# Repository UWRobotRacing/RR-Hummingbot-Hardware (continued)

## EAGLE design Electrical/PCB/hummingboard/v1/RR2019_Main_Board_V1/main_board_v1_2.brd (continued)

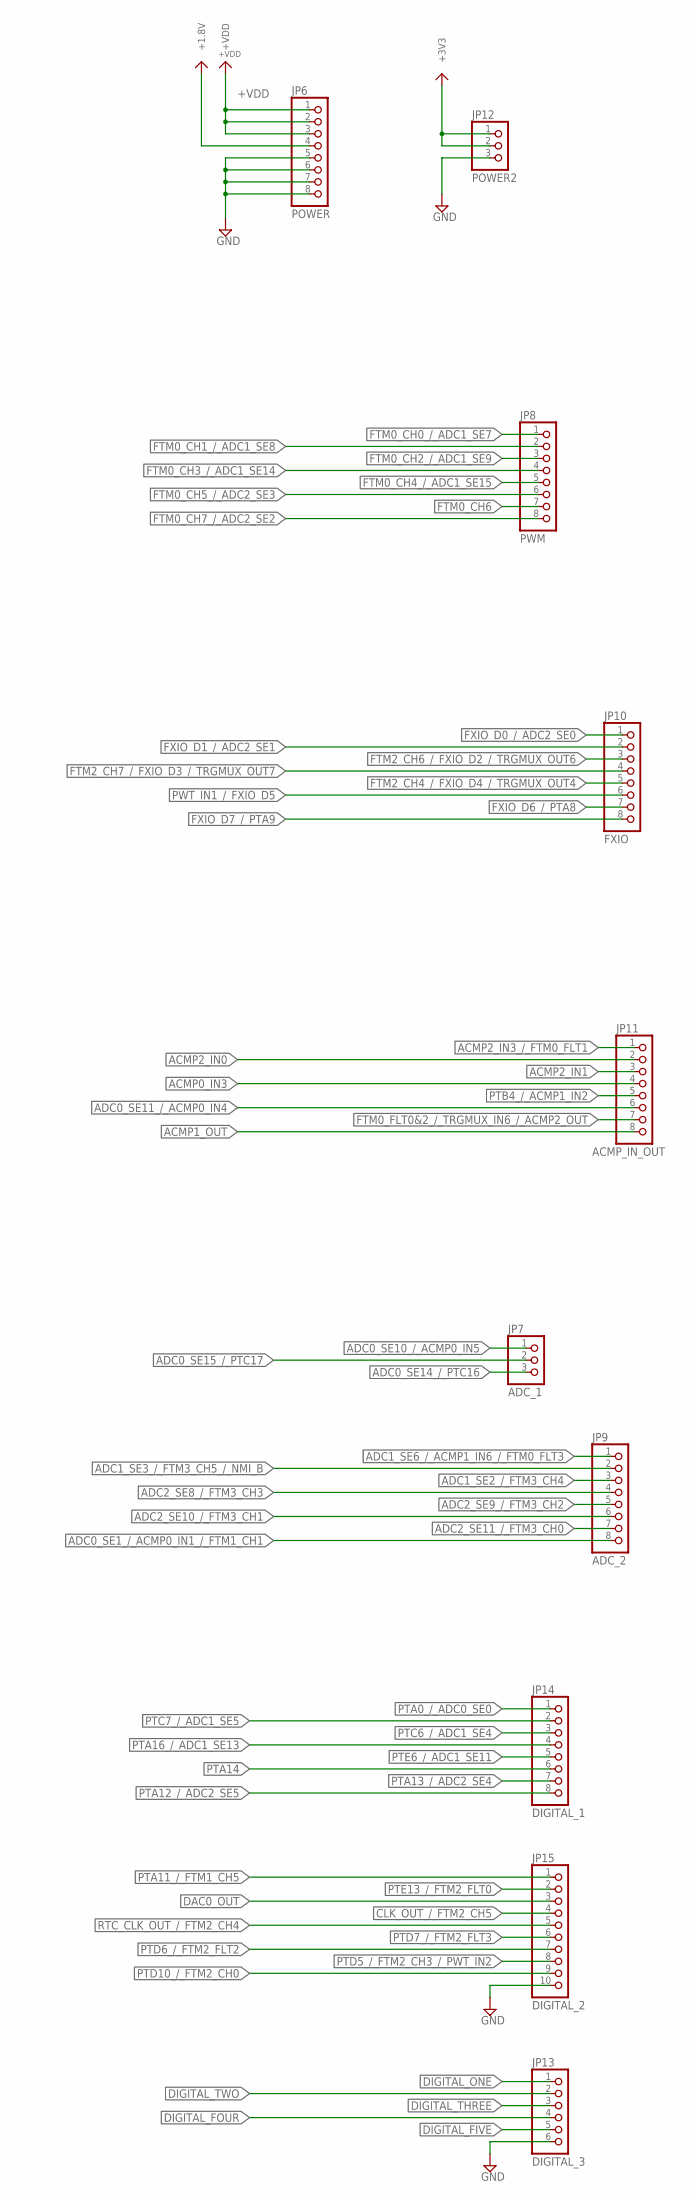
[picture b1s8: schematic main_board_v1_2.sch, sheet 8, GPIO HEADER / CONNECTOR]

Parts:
JP6: POWER; 1X08-BIG
JP7: ADC_1; 1X03
JP8: PWM; 1X08-BIG
JP9: ADC_2; 1X08-BIG
JP10: FXIO; 1X08-BIG
JP11: ACMP_IN_OUT; 1X08-BIG
JP12: POWER2; 1X03
JP13: DIGITAL_3; 1X06-BIG
JP14: DIGITAL_1; 1X08-BIG
JP15: DIGITAL_2; 1X10-BIG

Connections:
+1.8V: JP6.4; also elsewhere on the board
+3V3: JP12.1, JP12.2; also elsewhere on the board
+VDD: JP6.1, JP6.2, JP6.3; also elsewhere on the board
ACMP0_IN3: JP11.4; also elsewhere on the board
ACMP1_OUT: JP11.8; also elsewhere on the board
ACMP2_IN0: JP11.2; also elsewhere on the board
ACMP2_IN1: JP11.3; also elsewhere on the board
ACMP2_IN3_/_FTM0_FLT1: JP11.1; also elsewhere on the board
ADC0_SE1_/_ACMP0_IN1_/_FTM1_CH1: JP9.8; also elsewhere on the board
ADC0_SE10_/_ACMP0_IN5: JP7.1; also elsewhere on the board
ADC0_SE11_/_ACMP0_IN4: JP11.6; also elsewhere on the board
ADC0_SE14_/_PTC16: JP7.3; also elsewhere on the board
ADC0_SE15_/_PTC17: JP7.2; also elsewhere on the board
ADC1_SE2_/_FTM3_CH4: JP9.3; also elsewhere on the board
ADC1_SE3_/_FTM3_CH5_/_NMI_B: JP9.2; also elsewhere on the board
ADC1_SE6_/_ACMP1_IN6_/_FTM0_FLT3: JP9.1; also elsewhere on the board
ADC2_SE8_/_FTM3_CH3: JP9.4; also elsewhere on the board
ADC2_SE9_/_FTM3_CH2: JP9.5; also elsewhere on the board
ADC2_SE10_/_FTM3_CH1: JP9.6; also elsewhere on the board
ADC2_SE11_/_FTM3_CH0: JP9.7; also elsewhere on the board
CLK_OUT_/_FTM2_CH5: JP15.4; also elsewhere on the board
DAC0_OUT: JP15.3; also elsewhere on the board
DIGITAL_FIVE: JP13.5; also elsewhere on the board
DIGITAL_FOUR: JP13.4; also elsewhere on the board
DIGITAL_ONE: JP13.1; also elsewhere on the board
DIGITAL_THREE: JP13.3; also elsewhere on the board
DIGITAL_TWO: JP13.2; also elsewhere on the board
FTM0_CH0_/_ADC1_SE7: JP8.1; also elsewhere on the board
FTM0_CH1_/_ADC1_SE8: JP8.2; also elsewhere on the board
FTM0_CH2_/_ADC1_SE9: JP8.3; also elsewhere on the board
FTM0_CH3_/_ADC1_SE14: JP8.4; also elsewhere on the board
FTM0_CH4_/_ADC1_SE15: JP8.5; also elsewhere on the board
FTM0_CH5_/_ADC2_SE3: JP8.6; also elsewhere on the board
FTM0_CH6: JP8.7; also elsewhere on the board
FTM0_CH7_/_ADC2_SE2: JP8.8; also elsewhere on the board
FTM0_FLT0&2_/_TRGMUX_IN6_/_ACMP2_OUT: JP11.7; also elsewhere on the board
FTM2_CH4_/_FXIO_D4_/_TRGMUX_OUT4: JP10.5; also elsewhere on the board
FTM2_CH6_/_FXIO_D2_/_TRGMUX_OUT6: JP10.3; also elsewhere on the board
FTM2_CH7_/_FXIO_D3_/_TRGMUX_OUT7: JP10.4; also elsewhere on the board
FXIO_D0_/_ADC2_SE0: JP10.1; also elsewhere on the board
FXIO_D1_/_ADC2_SE1: JP10.2; also elsewhere on the board
FXIO_D6_/_PTA8: JP10.7; also elsewhere on the board
FXIO_D7_/_PTA9: JP10.8; also elsewhere on the board
GND: JP6.5, JP6.6, JP6.7, JP6.8, JP12.3, JP13.6, JP15.10; also elsewhere on the board
PTA0_/_ADC0_SE0: JP14.1; also elsewhere on the board
PTA11_/_FTM1_CH5: JP15.1; also elsewhere on the board
PTA12_/_ADC2_SE5: JP14.8; also elsewhere on the board
PTA13_/_ADC2_SE4: JP14.7; also elsewhere on the board
PTA14: JP14.6; also elsewhere on the board
PTA16_/_ADC1_SE13: JP14.4; also elsewhere on the board
PTB4_/_ACMP1_IN2: JP11.5; also elsewhere on the board
PTC6_/_ADC1_SE4: JP14.3; also elsewhere on the board
PTC7_/_ADC1_SE5: JP14.2; also elsewhere on the board
PTD5_/_FTM2_CH3_/_PWT_IN2: JP15.8; also elsewhere on the board
PTD6_/_FTM2_FLT2: JP15.7; also elsewhere on the board
PTD7_/_FTM2_FLT3: JP15.6; also elsewhere on the board
PTD10_/_FTM2_CH0: JP15.9; also elsewhere on the board
PTE6_/_ADC1_SE11: JP14.5; also elsewhere on the board
PTE13_/_FTM2_FLT0: JP15.2; also elsewhere on the board
PWT_IN1_/_FXIO_D5: JP10.6; also elsewhere on the board
RTC_CLK_OUT_/_FTM2_CH4: JP15.5; also elsewhere on the board

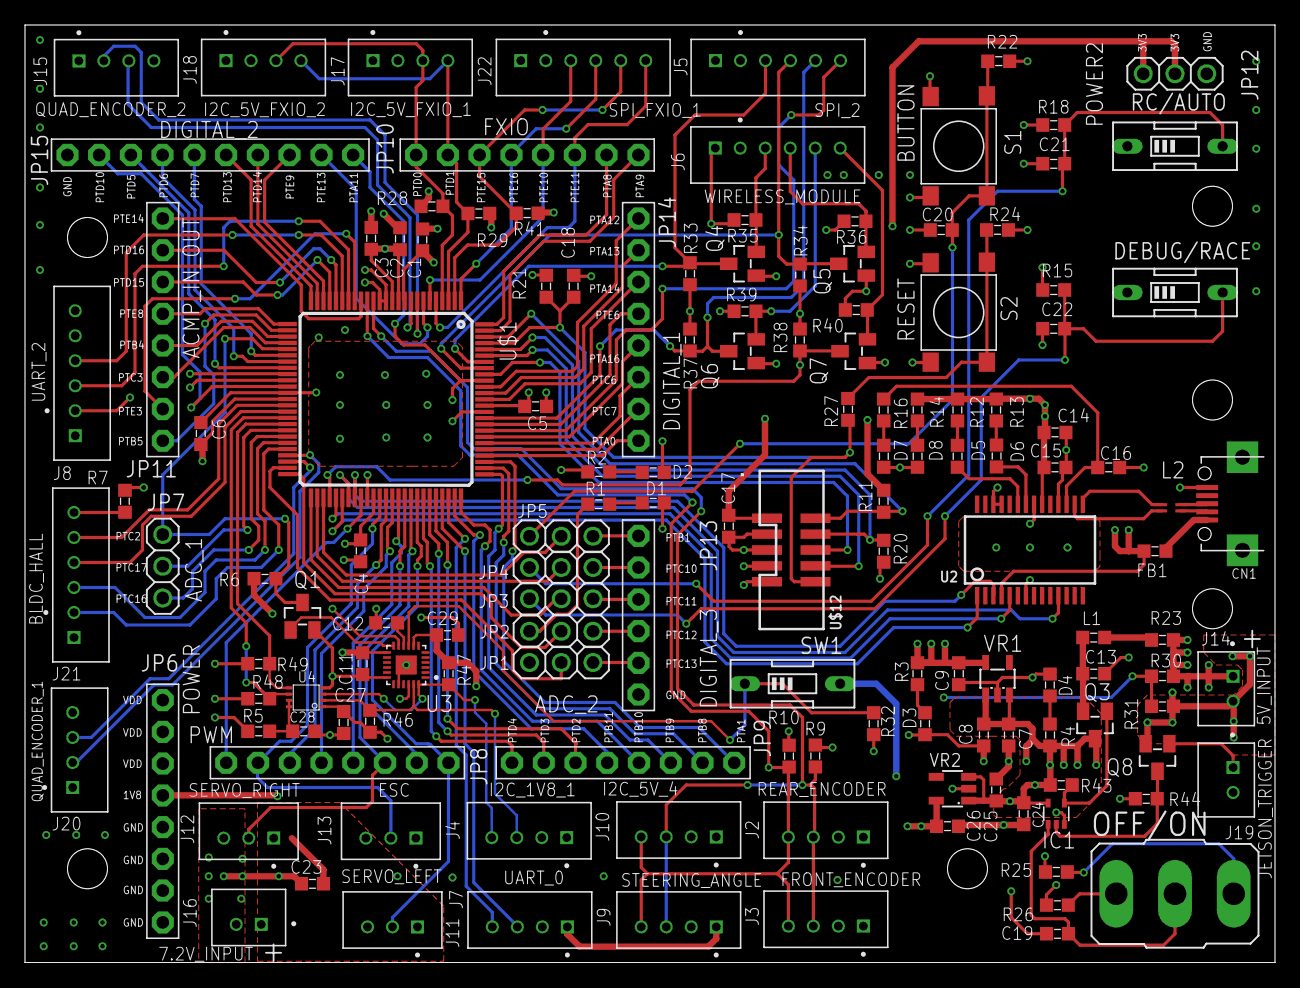
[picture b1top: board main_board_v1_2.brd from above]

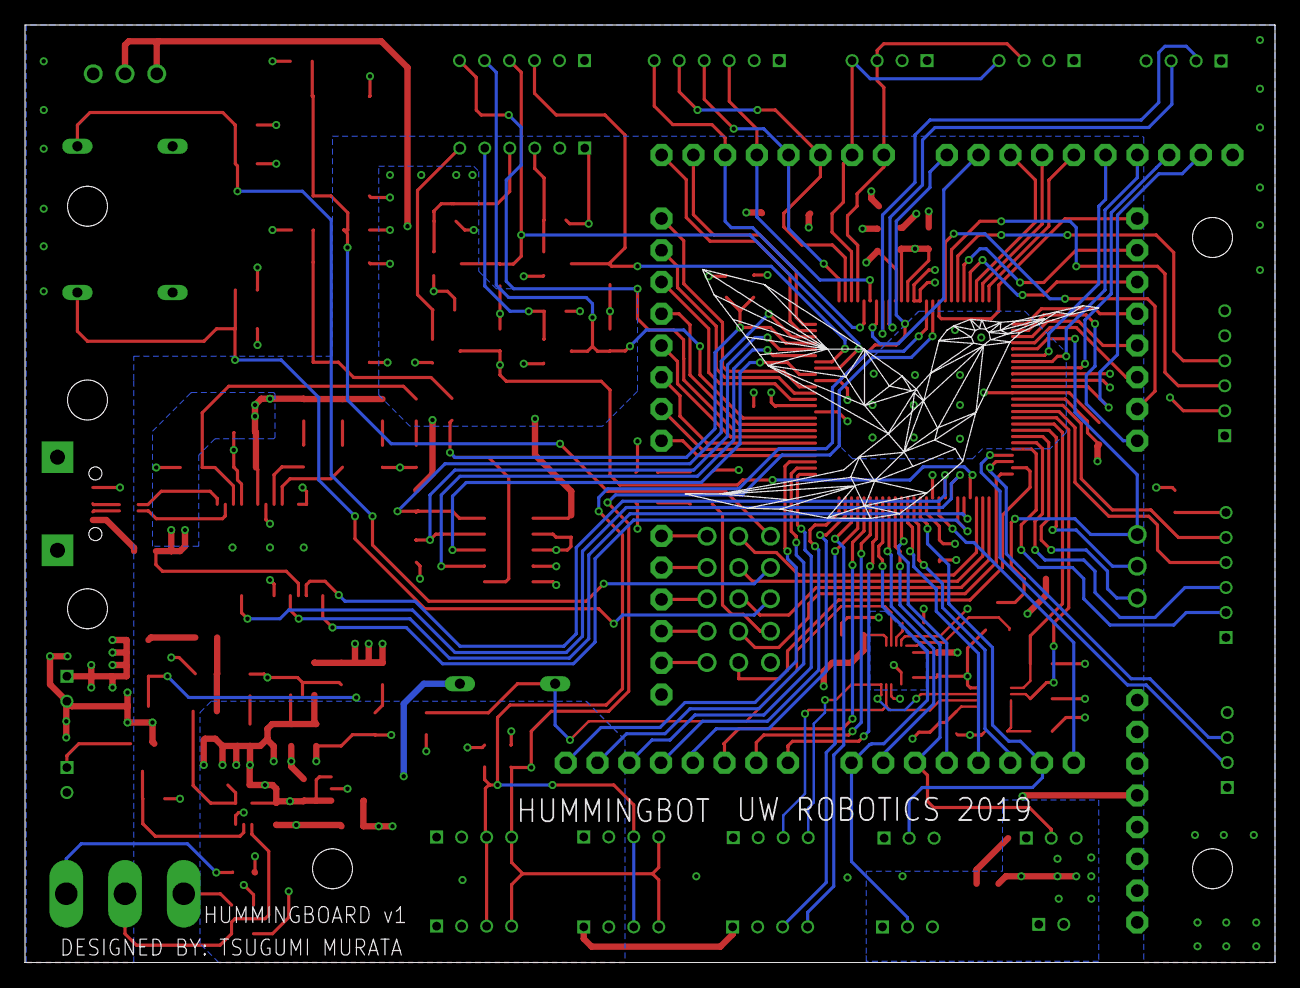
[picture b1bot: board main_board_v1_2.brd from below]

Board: 4 copper layers, 100.0 x 75.0 mm, 143 parts (2 on the bottom side), 142 nets.

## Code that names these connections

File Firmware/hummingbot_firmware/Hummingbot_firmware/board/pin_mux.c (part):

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BOARD_InitPins:
- options: {callFromInitBoot: 'true', coreID: core0, enableClock: 'true'}
- pin_list:
  - {pin_num: '1', peripheral: FLEXIO, signal: 'D, 3', pin_signal: PTE16/FTM2_CH7/FXIO_D3/TRGMUX_OUT7}
  - {pin_num: '2', peripheral: FLEXIO, signal: 'D, 2', pin_signal: PTE15/FTM2_CH6/FXIO_D2/TRGMUX_OUT6}
  - {pin_num: '3', peripheral: FLEXIO, signal: 'D, 1', pin_signal: ADC2_SE1/PTD1/FTM0_CH3/LPSPI1_SIN/FTM2_CH1/FXIO_D1/TRGMUX_OUT2}
  - {pin_num: '4', peripheral: FLEXIO, signal: 'D, 0', pin_signal: ADC2_SE0/PTD0/FTM0_CH2/LPSPI1_SCK/FTM2_CH0/FXIO_D0/TRGMUX_OUT1}
  - {pin_num: '5', peripheral: FLEXIO, signal: 'D, 5', pin_signal: ADC2_SE13/PTE11/PWT_IN1/LPTMR0_ALT1/FTM2_CH5/FXIO_D5/TRGMUX_OUT5}
  - {pin_num: '6', peripheral: FLEXIO, signal: 'D, 4', pin_signal: ADC2_SE12/PTE10/CLKOUT/FTM2_CH4/FXIO_D4/TRGMUX_OUT4}
  - {pin_num: '7', peripheral: GPIOE, signal: 'GPIO, 13', pin_signal: PTE13/FTM2_FLT0}
  - {pin_num: '8', peripheral: FTM2, signal: 'QD_PH, A', pin_signal: PTE5/TCLK2/FTM2_QD_PHA/FTM2_CH3/FXIO_D7/EWM_IN}
  - {pin_num: '9', peripheral: FTM2, signal: 'QD_PH, B', pin_signal: PTE4/BUSOUT/FTM2_QD_PHB/FTM2_CH2/FXIO_D6/EWM_OUT_b}
  - {pin_num: '10', peripheral: SUPPLY, signal: 'VDD, 0', pin_signal: VDD10}
  - {pin_num: '14', peripheral: SUPPLY, signal: 'VSS, 1', pin_signal: VSS15}
  - {pin_num: '15', peripheral: LPI2C0, signal: SCL, pin_signal: EXTAL/PTB7/LPI2C0_SCL}
  - {pin_num: '16', peripheral: LPI2C0, signal: SDA, pin_signal: XTAL/PTB6/LPI2C0_SDA}
  - {pin_num: '17', peripheral: CMP2, signal: 'IN, 3', pin_signal: ACMP2_IN3/PTE14/FTM0_FLT1/FTM2_FLT1}
  - {pin_num: '18', peripheral: CMP2, signal: OUT, pin_signal: PTE3/FTM0_FLT0/LPUART2_RTS/FTM2_FLT0/TRGMUX_IN6/ACMP2_OUT}
  - {pin_num: '19', peripheral: LPUART2, signal: TX, pin_signal: PTE12/FTM0_FLT3/LPUART2_TX}
  - {pin_num: '20', peripheral: LPUART2, signal: RX, pin_signal: PTD17/FTM0_FLT2/LPUART2_RX}
  - {pin_num: '21', peripheral: CMP2, signal: 'IN, 0', pin_signal: ACMP2_IN0/PTD16/FTM0_CH1}
  - {pin_num: '22', peripheral: CMP2, signal: 'IN, 1', pin_signal: ACMP2_IN1/PTD15/FTM0_CH0}
  - {pin_num: '23', peripheral: DAC0, signal: OUT, pin_signal: ACMP2_IN2/DAC0_OUT/PTE9/FTM0_CH7/LPUART2_CTS}
  - {pin_num: '24', peripheral: FTM2, signal: 'CH, 5', pin_signal: PTD14/FTM2_CH5/CLKOUT}
  - {pin_num: '25', peripheral: FTM2, signal: 'CH, 4', pin_signal: PTD13/FTM2_CH4/RTC_CLKOUT}
  - {pin_num: '26', peripheral: CMP0, signal: 'IN, 3', pin_signal: ACMP0_IN3/PTE8/FTM0_CH6}
  - {pin_num: '27', peripheral: CMP1, signal: OUT, pin_signal: PTB5/FTM0_CH5/LPSPI0_PCS1/TRGMUX_IN0/ACMP1_OUT}
  - {pin_num: '28', peripheral: CMP1, signal: 'IN, 2', pin_signal: ACMP1_IN2/PTB4/FTM0_CH4/LPSPI0_SOUT/TRGMUX_IN1}
  - {pin_num: '29', peripheral: CMP0, signal: 'IN, 4', pin_signal: ADC0_SE11/ACMP0_IN4/EXTAL32/PTC3/FTM0_CH3}
  - {pin_num: '30', peripheral: ADC0, signal: 'SE, 10', pin_signal: ADC0_SE10/ACMP0_IN5/XTAL32/PTC2/FTM0_CH2}
  - {pin_num: '31', peripheral: GPIOD, signal: 'GPIO, 7', pin_signal: PTD7/LPUART2_TX/FTM2_FLT3}
  - {pin_num: '32', peripheral: GPIOD, signal: 'GPIO, 6', pin_signal: PTD6/LPUART2_RX/FTM2_FLT2}
  - {pin_num: '33', peripheral: GPIOD, signal: 'GPIO, 5', pin_signal: PTD5/FTM2_CH3/LPTMR0_ALT2/FTM2_FLT1/PWT_IN2/TRGMUX_IN7}
  - {pin_num: '34', peripheral: LPUART2, signal: RTS, pin_signal: PTD12/FTM2_CH2/LPI2C1_HREQ/LPUART2_RTS}
  - {pin_num: '35', peripheral: LPUART2, signal: CTS, pin_signal: PTD11/FTM2_CH1/FTM2_QD_PHA/LPUART2_CTS}
  - {pin_num: '36', peripheral: GPIOD, signal: 'GPIO, 10', pin_signal: PTD10/FTM2_CH0/FTM2_QD_PHB}
  - {pin_num: '37', peripheral: SUPPLY, signal: 'VSS, 2', pin_signal: VSS38}
  - {pin_num: '39', peripheral: FTM1, signal: 'CH, 7', pin_signal: ADC0_SE9/ACMP1_IN3/PTC1/FTM0_CH1/FTM1_CH7}
  - {pin_num: '38', peripheral: SUPPLY, signal: 'VDD, 1', pin_signal: VDD39}
  - {pin_num: '40', peripheral: FTM1, signal: 'CH, 6', pin_signal: ADC0_SE8/ACMP1_IN4/PTC0/FTM0_CH0/FTM1_CH6}
  - {pin_num: '41', peripheral: LPI2C1, signal: SCL, pin_signal: ACMP1_IN5/PTD9/LPI2C1_SCL/FTM2_FLT3/FTM1_CH5}
  - {pin_num: '42', peripheral: LPI2C1, signal: SDA, pin_signal: PTD8/LPI2C1_SDA/FTM2_FLT2/FTM1_CH4}
  - {pin_num: '43', peripheral: ADC0, signal: 'SE, 15', pin_signal: ADC0_SE15/PTC17/FTM1_FLT3/LPI2C1_SCLS}
  - {pin_num: '44', peripheral: ADC0, signal: 'SE, 14', pin_signal: ADC0_SE14/PTC16/FTM1_FLT2/LPI2C1_SDAS}
  - {pin_num: '45', peripheral: FTM1, signal: 'CH, 3', pin_signal: ADC0_SE13/ACMP2_IN4/PTC15/FTM1_CH3}
  - {pin_num: '46', peripheral: FTM1, signal: 'CH, 2', pin_signal: ADC0_SE12/ACMP2_IN5/PTC14/FTM1_CH2}
  - {pin_num: '47', peripheral: FTM1, signal: 'QD_PH, A', pin_signal: ADC0_SE7/PTB3/FTM1_CH1/LPSPI0_SIN/FTM1_QD_PHA/TRGMUX_IN2}
  - {pin_num: '48', peripheral: FTM1, signal: 'QD_PH, B', pin_signal: ADC0_SE6/PTB2/FTM1_CH0/LPSPI0_SCK/FTM1_QD_PHB/TRGMUX_IN3}
  - {pin_num: '49', peripheral: GPIOC, signal: 'GPIO, 13', pin_signal: PTC13/FTM3_CH7/FTM2_CH7}
  - {pin_num: '50', peripheral: GPIOC, signal: 'GPIO, 12', pin_signal: PTC12/FTM3_CH6/FTM2_CH6}
  - {pin_num: '51', peripheral: GPIOC, signal: 'GPIO, 11', pin_signal: PTC11/FTM3_CH5}
  - {pin_num: '52', peripheral: GPIOC, signal: 'GPIO, 10', pin_signal: PTC10/FTM3_CH4}
  - {pin_num: '53', peripheral: GPIOB, signal: 'GPIO, 1', pin_signal: ADC0_SE5/ADC1_SE15/PTB1/LPUART0_TX/LPSPI0_SOUT/TCLK0}
  - {pin_num: '54', peripheral: LPSPI0, signal: PCS0, pin_signal: ADC0_SE4/ADC1_SE14/PTB0/LPUART0_RX/LPSPI0_PCS0/LPTMR0_ALT3/PWT_IN3}
  - {pin_num: '55', peripheral: LPUART1, signal: TX, pin_signal: ADC2_SE15/PTC9/LPUART1_TX/FTM1_FLT1/LPUART0_RTS}
  - {pin_num: '56', peripheral: LPUART1, signal: RX, pin_signal: ADC2_SE14/PTC8/LPUART1_RX/FTM1_FLT0/LPUART0_CTS}
  - {pin_num: '57', peripheral: LPUART1, signal: RTS, pin_signal: ADC0_SE3/ACMP1_IN1/PTA7/FTM0_FLT2/RTC_CLKIN/LPUART1_RTS}
  - {pin_num: '58', peripheral: LPUART1, signal: CTS, pin_signal: ADC0_SE2/ACMP1_IN0/PTA6/FTM0_FLT1/LPSPI1_PCS1/LPUART1_CTS}
  - {pin_num: '59', peripheral: FTM0, signal: 'CH, 7', pin_signal: ADC2_SE2/ACMP2_IN6/PTE7/FTM0_CH7/FTM3_FLT0}
  - {pin_num: '61', peripheral: SUPPLY, signal: 'VDD, 2', pin_signal: VDD62}
  - {pin_num: '60', peripheral: SUPPLY, signal: 'VSS, 3', pin_signal: VSS61}
  - {pin_num: '62', peripheral: FTM0, signal: 'CH, 6', pin_signal: PTA17/FTM0_CH6/FTM3_FLT0/EWM_OUT_b}
  - {pin_num: '63', peripheral: FTM0, signal: 'CH, 5', pin_signal: ADC2_SE3/PTB17/FTM0_CH5/LPSPI1_PCS3}
  - {pin_num: '64', peripheral: FTM0, signal: 'CH, 4', pin_signal: ADC1_SE15/PTB16/FTM0_CH4/LPSPI1_SOUT}
  - {pin_num: '65', peripheral: FTM0, signal: 'CH, 3', pin_signal: ADC1_SE14/PTB15/FTM0_CH3/LPSPI1_SIN}
  - {pin_num: '66', peripheral: FTM0, signal: 'CH, 2', pin_signal: ADC1_SE9/ADC2_SE9/PTB14/FTM0_CH2/LPSPI1_SCK}
  - {pin_num: '67', peripheral: FTM0, signal: 'CH, 1', pin_signal: ADC1_SE8/ADC2_SE8/PTB13/FTM0_CH1/FTM3_FLT1}
  - {pin_num: '68', peripheral: FTM0, signal: 'CH, 0', pin_signal: ADC1_SE7/PTB12/FTM0_CH0/FTM3_FLT2}
  - {pin_num: '69', peripheral: ADC1, signal: 'SE, 6', pin_signal: ADC1_SE6/ACMP1_IN6/PTD4/FTM0_FLT3/FTM3_FLT3}
  - {pin_num: '70', peripheral: ADC1, signal: 'SE, 3', pin_signal: ADC1_SE3/PTD3/FTM3_CH5/LPSPI1_PCS0/FXIO_D5/TRGMUX_IN4/NMI_b}
  - {pin_num: '71', peripheral: ADC1, signal: 'SE, 2', pin_signal: ADC1_SE2/PTD2/FTM3_CH4/LPSPI1_SOUT/FXIO_D4/TRGMUX_IN5}
  - {pin_num: '72', peripheral: LPUART0, signal: TX, pin_signal: ADC1_SE1/PTA3/FTM3_CH1/LPI2C0_SCL/EWM_IN/LPUART0_TX}
  - {pin_num: '73', peripheral: LPUART0, signal: RX, pin_signal: ADC1_SE0/PTA2/FTM3_CH0/LPI2C0_SDA/EWM_OUT_b/LPUART0_RX}
  - {pin_num: '74', peripheral: ADC2, signal: 'SE, 8', pin_signal: ADC2_SE8/PTB11/FTM3_CH3/LPI2C0_HREQ}
  - {pin_num: '75', peripheral: ADC2, signal: 'SE, 9', pin_signal: ADC2_SE9/PTB10/FTM3_CH2/LPI2C0_SDAS}
  - {pin_num: '76', peripheral: ADC2, signal: 'SE, 10', pin_signal: ADC2_SE10/PTB9/FTM3_CH1/LPI2C0_SCLS}
  - {pin_num: '77', peripheral: ADC2, signal: 'SE, 11', pin_signal: ADC2_SE11/PTB8/FTM3_CH0}
  - {pin_num: '78', peripheral: ADC0, signal: 'SE, 1', pin_signal: ADC0_SE1/ACMP0_IN1/PTA1/FTM1_CH1/LPI2C0_SDAS/FXIO_D3/FTM1_QD_PHA/LPUART0_RTS/TRGMUX_OUT0}
  - {pin_num: '80', peripheral: GPIOC, signal: 'GPIO, 7', pin_signal: ADC1_SE5/PTC7/LPUART1_TX/FTM3_CH3}
  - {pin_num: '79', peripheral: ADC0, signal: 'SE, 0', pin_signal: ADC0_SE0/ACMP0_IN0/PTA0/FTM2_CH1/LPI2C0_SCLS/FXIO_D2/FTM2_QD_PHA/LPUART0_CTS/TRGMUX_OUT3}
  - {pin_num: '81', peripheral: GPIOC, signal: 'GPIO, 6', pin_signal: ADC1_SE4/PTC6/LPUART1_RX/FTM3_CH2}
  - {pin_num: '82', peripheral: GPIOA, signal: 'GPIO, 16', pin_signal: ADC1_SE13/PTA16/FTM1_CH3/LPSPI1_PCS2}
  - {pin_num: '83', peripheral: LPSPI0, signal: PCS3, pin_signal: ADC1_SE12/PTA15/FTM1_CH2/LPSPI0_PCS3}
  - {pin_num: '84', peripheral: GPIOE, signal: 'GPIO, 6', pin_signal: ADC1_SE11/ACMP0_IN6/PTE6/LPSPI0_PCS2/FTM3_CH7/LPUART1_RTS}
  - {pin_num: '85', peripheral: LPSPI0, signal: SOUT, pin_signal: ADC1_SE10/PTE2/LPSPI0_SOUT/LPTMR0_ALT3/FTM3_CH6/PWT_IN3/LPUART1_CTS}
  - {pin_num: '87', peripheral: SUPPLY, signal: 'VDD, 3', pin_signal: VDD88}
  - {pin_num: '86', peripheral: SUPPLY, signal: 'VSS, 4', pin_signal: VSS87}
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
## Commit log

2019-01-10 add new electrical
2019-01-10 add initial PCB files
2019-01-10 add library
2019-01-10 initial commit for power managment board
2019-01-12 Creating symbols for new power management ICs
2019-01-12 Created part for S1011AA0
2019-01-12 Created part for the 6V monitor and imported Boost part
2019-01-14 update on layout
2019-01-16 Adding SDKs for MCU chip
2019-01-17 added LM2940IMP-5.0 LDO to the library
2019-01-17 Added Spice models and simulation for boost converter
2019-01-17 simulation file added
2019-01-17 updated trace
2019-01-17 add CRS08 as model parameter
2019-01-17 add LM2940 component lib
2019-01-18 add encrypted model of LM2940
2019-01-18 regualr update
2019-01-18 Created device LMR64010 to library
2019-01-18 Started schematic for boost converter
2019-01-18 Imported a diode library
2019-01-18 Initial simulation of LDO
2019-01-22 add 5-3.3V logic level shift simulation
2019-01-22 added library for DC jack
2019-01-23 Updated the SVS for 11.1V
2019-01-23 Idk what i changed
2019-01-23 power supply fixed
2019-01-23 [Journey Begins From Here] + new simulations and PCBs
2019-01-23 [Repo Cleanup | .gitignore] + ignore DS_Store
2019-01-23 - removed all .DS_Store
2019-01-23 .gitignore
2019-01-24 library mod
2019-01-24 Adding MCU pin config for initial pin assignments
2019-01-24 deleted eagle library backup files, also added the dc jack library
2019-01-24 committing the deletion of the firmware folder since move to firmware repo is done
2019-01-24 add OR logic for power control
2019-01-25 add 1.8V LDO and IMU change to ICM-20948
2019-01-25 add 1.8 LDO and ICM-20948
2019-01-25 add ICM-20948 and 1.8V LDO
2019-01-26 signal connection complete
2019-01-26 add 1V8, 3V3, VUSB power plane
2019-01-27 add silkscreen for pin info
2019-01-27 add silkscreen on SOT23
2019-01-27 silkscreen complete for board
2019-01-28 change 2 switch to DIP and toggle smaller
2019-01-28 add toggle switch
2019-01-30 layout complete v.1
2019-01-30 layout and power planed modified, complete v2
2019-01-31 gerber file
2019-01-31 increase 7.2V power plane size
2019-02-07 add CAM JOB
2019-02-07 add desgin rule
2019-02-11 gerber generated for modified board
2019-02-11 remove inductor from 7.2V input / modify GND plane
2019-02-11 gerber of modified board
2019-02-11 add extra GND plane and via
2019-02-22 add filter values
2019-02-28 hummingboard_uart/led code
2019-03-01 PRINTF working, added button test code
2019-03-03 change clock config
2019-03-06 New SDK with RTOS and project with RTOS
2019-03-07 working freertos project
2019-03-07 added task
2019-03-07 another RTOS project
2019-03-07 [gitignore]
2019-03-07 [gitignore] - ignore Debug folder
2019-03-07 - ignore
2019-03-07 [Fresh Upload]
2019-03-13 simple i2c and spi test code
2019-03-20 fix the MOSI/MISO direction
2019-03-20 spi working
2019-03-22 modify ncs to clk timing issue for LPSPI
2019-03-22 add RF24 library (only converted the header for now)
2019-04-19 [Added Core Testing Codes on Slave Devices] + BLDC Motor buit-in Encoder interface + ESC Motor FM/FB control interface + Remote Controller recv/send interface
2019-04-25 [STABLE Controller code]
2019-04-26 Pushing steering code
2019-04-26 new files
2019-04-26 Create main_board_v1_2 (1).pdf
    Created new PDF for hummingboard
2019-04-29 [.gitignore] - ignore .vscode
2019-04-29 [Arduino Lib] + nrf24l01 lib shared
2019-05-04 [Removed old c libs] : they are incompatible
2019-05-04 + removed unused & incompatible libraries
2019-05-04 [nrf24l01 library] : partial library customized and optimized for m4 chip.
2019-05-04 [lib for rf24] + sth. isnt working with linking external source files
2019-05-17 [Finished RF24 Module] + TODO: SPI comm. not working
2019-05-18 [Cleaned up our code base, old code are in template folder]
2019-05-18 [add printf func]
2019-05-18 [rf24 implemented | compiled]
2019-05-19 [cleaned PWM steering servo code]
2019-05-19 [savedata changes]
2019-05-23 [Fixed UART]
2019-05-23 [Hummingboard banner + periodic task]
2019-05-23 + cannot get spi working
2019-05-23 code for testing concurrent led blinking and uart read/write
2019-05-31 [testing code] + working spi testing code
2019-06-09 [First Beta Version of RF24] + signals are quite similar to what to be expected + waiting to be tested once receiving new wireless modules
2019-06-09 Update README.md
    + provided some key notes on coding styles
2019-06-09 Update README.md
    added some resources reference
2019-06-11 using asynchronous callback uart echo
2019-06-11 transfer struct
2019-06-11 changed the struct to two float members
2019-06-11 testing receive
2019-06-11 send to uart0
2019-06-11 + some quick mod to confirm the code is working + TODO: need to polish some code
2019-06-11 [Servo Library] + servo library is working with a single servo, need further testing
2019-06-11 [Fixed merge conflicts]
2019-06-11 [Working FTM testing code for PWM] + resolution of 10us + need to make the code to an usable lib
2019-06-11 + minor changes
2019-06-11 changed delay Hz
2019-06-12 [Newborn: Vehicle Controller] + mainly to utilize servos to control vehicle + a place to put high level control algo.
2019-06-13 [Vehicle Controller Implemented] + implemented interpreatation layer that will take care of vc + TODO: last part: pipe rf24 command to vc
2019-06-15 [A COMPLETE implementation of remote controller & esc] + finished/preserved all pipelines [TODOs] + need to add coordination + TBT + need to find proper gpios to use + need to doc. & Comment
2019-06-15 + add a line of TODO, so you guys know where to change gpio preference
2019-06-15 + tested & modified some code, Vehicle Controller is now in operation + 100% guarantee within 100us accuracy
2019-06-16 [fully tested code] + rf24 working along with vehicle controller
2019-06-16 testing configuration for servo
2019-06-22 Test RC with SERVO and THROTTLE
2019-06-22 Testing new uart package
2019-06-22 Revert "changed delay Hz"
    This reverts commit be017b7ede7445742c1925ef6e1ec300ba6ca1b5.
2019-06-22 Revert "Revert "changed delay Hz""
    This reverts commit a04eea6618b822f5b9f321d916be3b6432172fad.
2019-06-22 Revert "Testing new uart package"
    This reverts commit 21b04ecc9019c2e1dcf3890a7659336fd4f0c8ee.
2019-06-22 Revert "Revert "Testing new uart package""
    This reverts commit 29442495091cf7c65fd03fabb72ae17aaa520000.
2019-06-22 2 uint16_t works
2019-06-22 FIXED UART0 PROBLEMS
2019-06-22 Working UART CODE
2019-06-25 Implemented uart code without ringbuffer
2019-06-25 making the task frequency higher than Jetson frequency helped sync
2019-06-25 + new clk config for servo, enabling 20us resolution without blocking + new feature: TBI, unfinished implementation of joystick mapping into VC controller + configurations defined
2019-06-26 [New Feature / Joystick mapping layer in VC] + the VC will handle joystick mapping
2019-06-28 Uart works
2019-06-29 works with 255 sync character
2019-06-30 added comments
2019-07-03 + Supposed to use hardware pwm
2019-07-03 test
2019-07-03 jerome helo
2019-07-03 Last working changes
2019-07-03 Revert "jerome helo"
    This reverts commit 6a89c1981ca6536f5d6b027214bad50dcafaf769.
2019-07-04 [Modified for ground test] + fixed freewheeling pulses
2019-07-04 Test code with fixed controller
2019-07-09 Changed the esc frequency back to 50 Hz
2019-07-09 UART struct added, changed max ESC PWM and deadband
2019-07-10 + some changes on vc controller
2019-07-11 + removed logs for pw_us
2019-07-11 + implement uart
2019-07-12 a few changes to make it build
2019-07-12 +working
2019-07-13 [UART SEMI WORKING | Need sync barrier]
2019-07-13 :wq+ added
2019-07-13 + re
2019-07-13 + increase cycle time
2019-07-13 + working serialization
2019-07-13 i+ calibration mode
2019-07-13 + implemented reversing double-tick mechanism & fwd&rev braking
2019-07-13 + compiled
2019-07-13 i+ calibration
2019-07-13 calibrated steering and throttle
2019-07-13 + estop successfully, + uart echo
2019-07-14 + config gpio40 as debug led
2019-07-14 + non blocking deserialization + ._. why, arduino, why you do this to me??????????? 1s blocking for readString?????????
2019-07-14 + enabled debug mode with echo + fixed lost controller t 500ms, and fix its behaviour
2019-07-14 + only turn on uart when auto mode
2019-07-14 +fixed err
2019-07-14 + interrupt block read
2019-07-14 + unit test for uart
2019-07-14 + gitignore python env
2019-07-14 + ignore venv
2019-07-14 + update ignore
2019-07-14 + working uart version
2019-11-14 + controller object adn parallel task created
2019-11-14 + m4 uart communication
